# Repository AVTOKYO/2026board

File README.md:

# AVTOKYO 2026 Hackable Board

[English](README_EN.md)

no drink, no hack

| 未実装の基板（裏面・表面） | 赤LEDを付けた作例 |
|---|---|
|  |  |

**Assembly guide / 作り方 — [日本語](docs/ASSEMBLY_JA.md) · [English](docs/ASSEMBLY_EN.md)**

AVTOKYOのドット絵ロゴをモチーフにした、自由に工作・改造して楽しむPCBです。部品を付けずにチャームとして使うのも、LEDや好きな回路を追加するのも自由です。

組み立て説明では、赤いLEDを2個点灯させるシンプルな例を紹介しています。ATtiny402を追加すると、プログラムで点滅を変えられます。

**LEDを付けてみたい方は、[基本の作り方](docs/ASSEMBLY_JA.md)をご覧ください。**

| 内容 | ファイル |
|---|---|
| 基本の組み立て | [組立説明書](docs/ASSEMBLY_JA.md) |
| 用意する部品 | [部品表](docs/PARTS_JA.md) |
| MCUを追加する工作 | [改造ガイド](docs/HACK_JA.md) |
| 書き込みと点滅プログラム | [ファームウェア説明](firmware/README_JA.md) |
| 裏蓋・ケース | [固定方法・STL](case/README.md) |
| 基板を発注する | [製造手順](manufacturing/README.md) |
| 最終製造用データ | [Rev M Gerber ZIP](manufacturing/AVTOKYO_LED_Charm_RevM_FINAL_JLCPCB.zip) |
| 編集する基板データ | [KiCad PCB](hardware/AVTOKYO_LED_Charm.kicad_pcb)・[回路図](hardware/AVTOKYO_LED_Charm.kicad_sch) |

回路図・基板データはKiCad 10で保存しています。ファイル一式をダウンロードしてから、hardware内のプロジェクトを開いてください。

## 確認状況

製造用データは回路図との照合を含むDRC・ERCを通過しています。検査結果はvalidationに収録しています。Rev Mの実機組立・MCU書込については最終確認結果が未記録です。

## ライセンスと改造

製作・改造・再配布・販売は、各ライセンスの条件に従って自由に行えます。[ライセンスの説明](docs/LICENSE_JA.md)と[ロゴ利用条件](LOGO_POLICY.md)をご覧ください。ケースSTLも、作者の同意により基板と同じCERN-OHL-P-2.0です。

組み立て説明は最もシンプルな構成の一例です。LEDの変更や部品の追加、MCUによる点滅など、自由に改造して楽しんでください。

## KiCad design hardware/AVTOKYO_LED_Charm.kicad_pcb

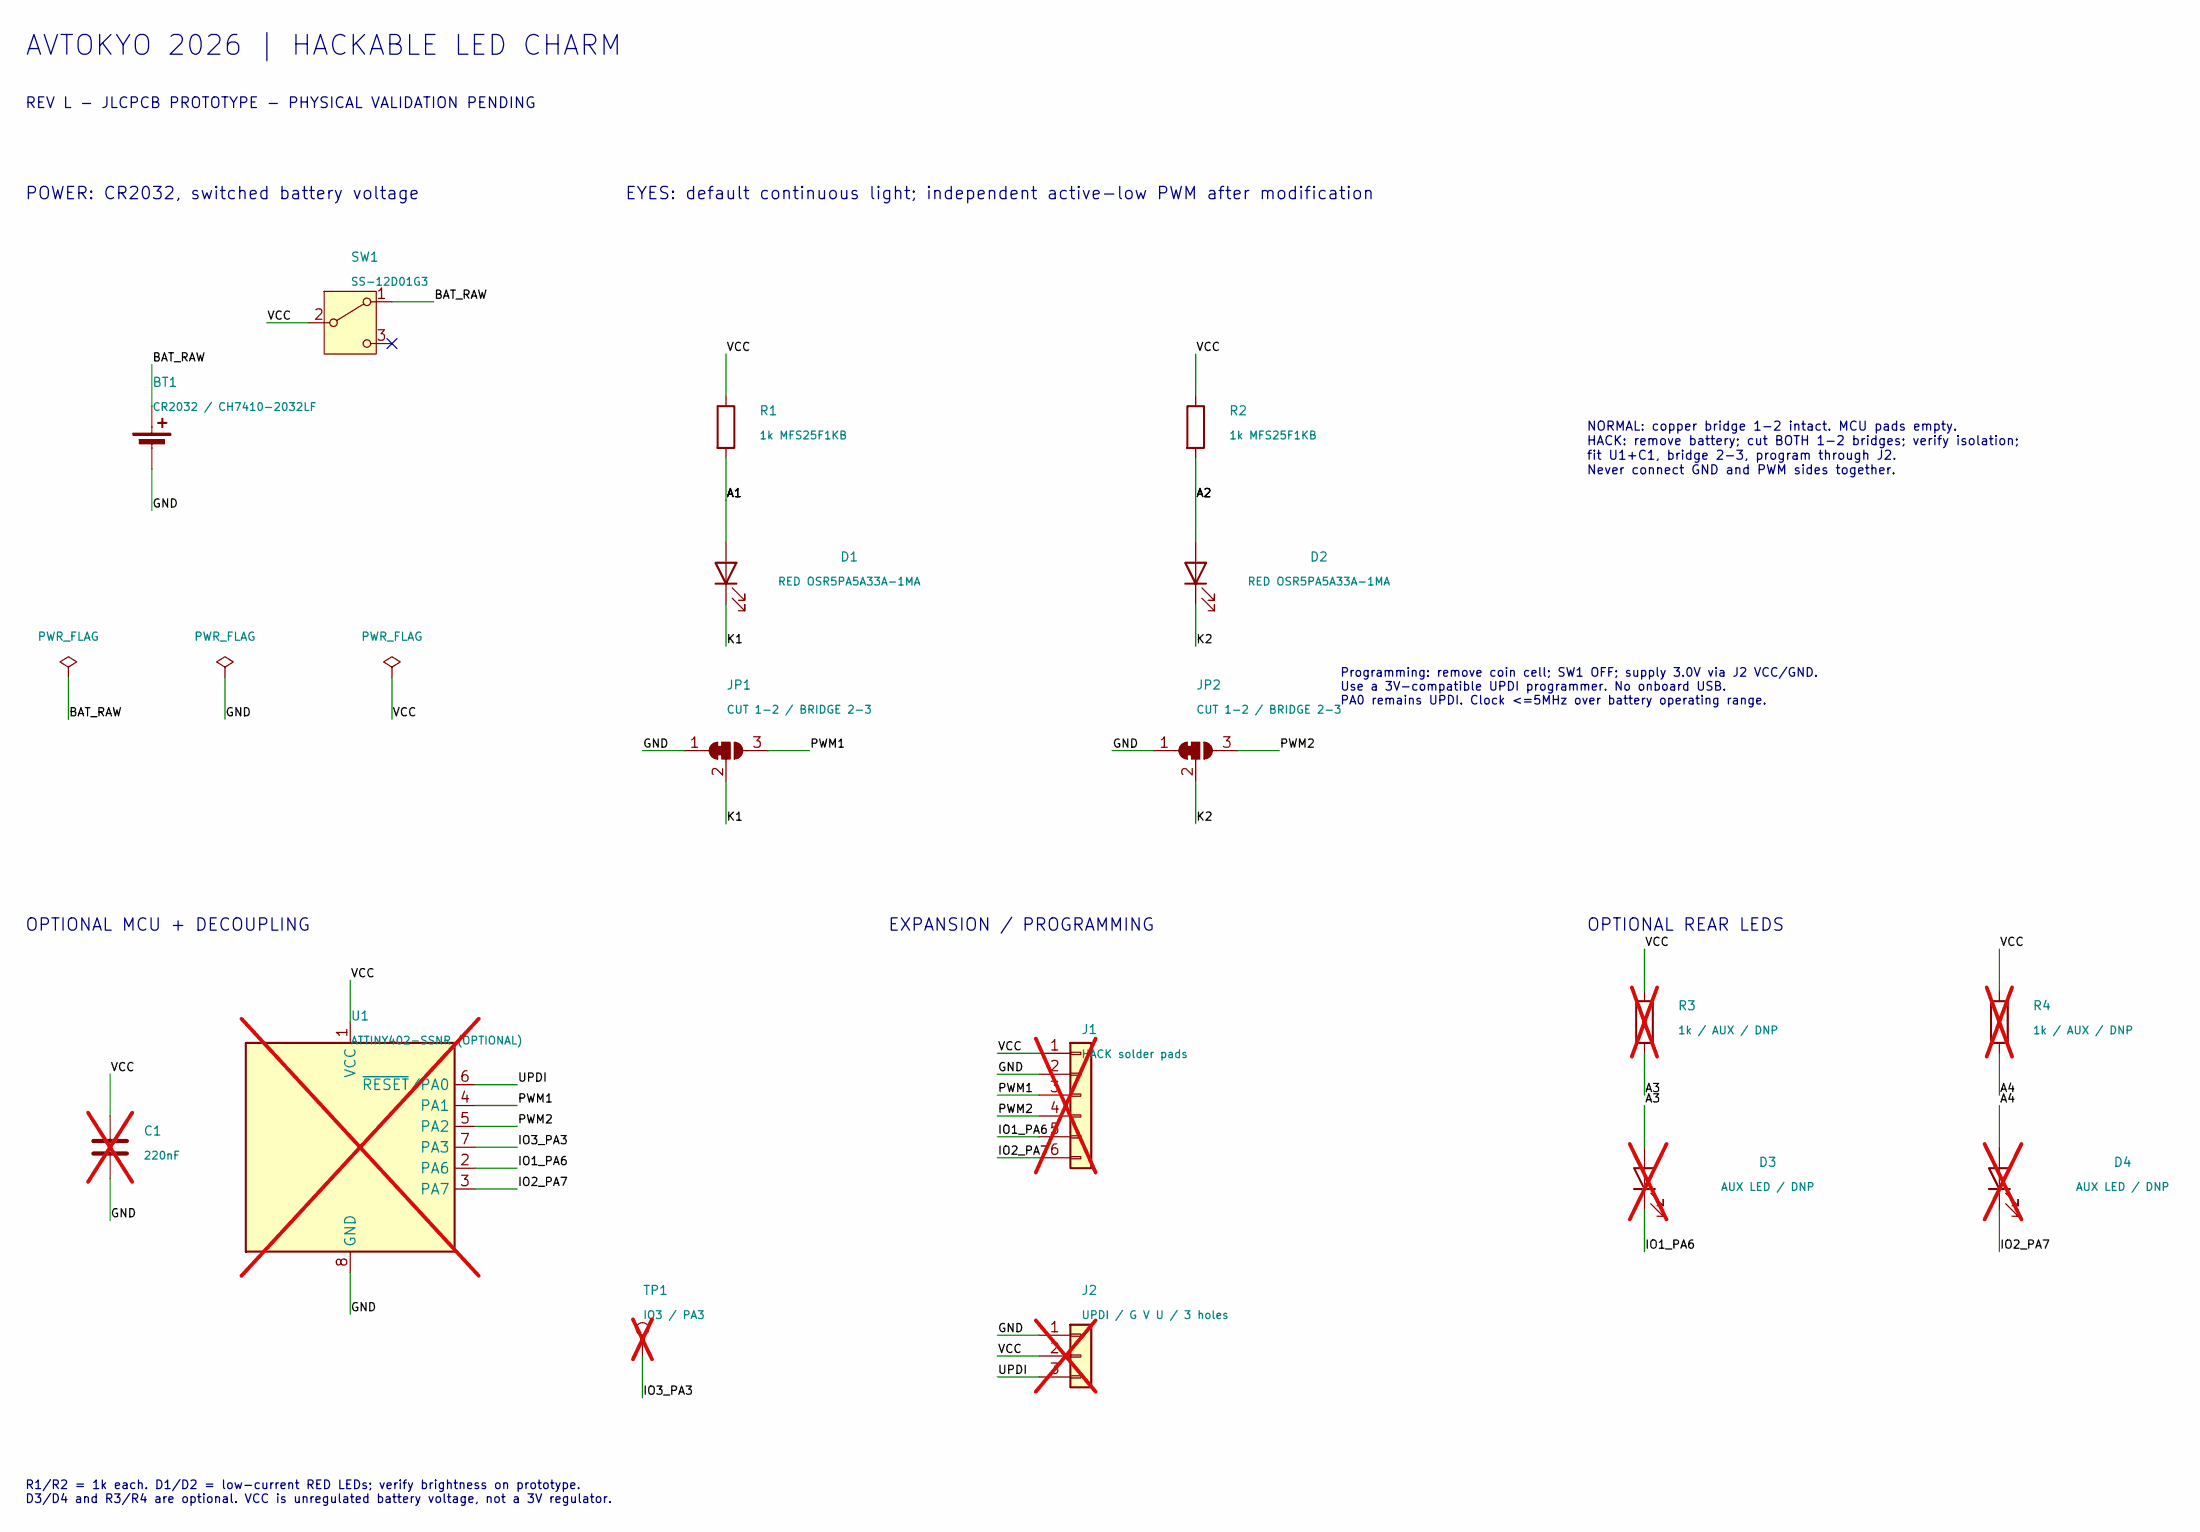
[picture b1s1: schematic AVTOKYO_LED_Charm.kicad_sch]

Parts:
BT1: CR2032 / CH7410-2032LF; BatteryHolder_CH7410_2032LF
C1: 220nF; C_0805_2012Metric_Pad1.18x1.45mm_HandSolder; not fitted
D1, D2: RED OSR5PA5A33A-1MA; LED_D5.0mm
D3, D4: AUX LED / DNP; LED_0805_2012Metric_Pad1.15x1.40mm_HandSolder; not fitted
J1: HACK solder pads; SolderPort_1x06_P2mm; not fitted
J2: UPDI / G V U / 3 holes; UPDI_1x03_P2.54mm_THT; not fitted
JP1, JP2: CUT 1-2 / BRIDGE 2-3; SolderJumper-3_P1.3mm_Bridged12_Pad1.0x1.5mm
R1, R2: 1k MFS25F1KB; R_Axial_DIN0204_L3.6mm_D1.6mm_P7.62mm_Horizontal
R3, R4: 1k / AUX / DNP; R_0805_2012Metric_Pad1.20x1.40mm_HandSolder; not fitted
SW1: SS-12D01G3; SW_SS12D01G3_RightAngle
TP1: IO3 / PA3; TestPoint_Pad_D1.5mm; not fitted
U1: ATTINY402-SSNR (OPTIONAL); SOIC-8_3.9x4.9mm_P1.27mm; not fitted

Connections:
/A1: D1.2 (A), R1.2
/A2: D2.2 (A), R2.2
/A3: D3.2 (A), R3.2
/A4: D4.2 (A), R4.2
/BAT_RAW: BT1.1 (+), SW1.1 (A)
/GND: BT1.2 (-), C1.2, J1.2, J2.1, JP1.1 (A), JP2.1 (A), U1.8 (GND)
/IO1_PA6: D3.1 (K), J1.5, U1.2 (PA6)
/IO2_PA7: D4.1 (K), J1.6, U1.3 (PA7)
/IO3_PA3: TP1.1, U1.7 (PA3)
/K1: D1.1 (K), JP1.2 (C)
/K2: D2.1 (K), JP2.2 (C)
/PWM1: J1.3, JP1.3 (B), U1.4 (PA1)
/PWM2: J1.4, JP2.3 (B), U1.5 (PA2)
/UPDI: J2.3, U1.6 (~RESET/PA0)
/VCC: C1.1, J1.1, J2.2, R1.1, R2.1, R3.1, R4.1, SW1.2 (B), U1.1 (VCC)

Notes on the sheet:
AVTOKYO 2026 | HACKABLE LED CHARM
REV L - JLCPCB PROTOTYPE - PHYSICAL VALIDATION PENDING
POWER: CR2032, switched battery voltage
EYES: default continuous light; independent active-low PWM after modification
OPTIONAL MCU + DECOUPLING
EXPANSION / PROGRAMMING
OPTIONAL REAR LEDS
NORMAL: copper bridge 1-2 intact. MCU pads empty. HACK: remove battery; cut BOTH 1-2 bridges; verify isolation; fit U1+C1, bridge 2-3, program through J2. Never connect GND and PWM sides together.
Programming: remove coin cell; SW1 OFF; supply 3.0V via J2 VCC/GND. Use a 3V-compatible UPDI programmer. No onboard USB. PA0 remains UPDI. Clock <=5MHz over battery operating range.
R1/R2 = 1k each. D1/D2 = low-current RED LEDs; verify brightness on prototype. D3/D4 and R3/R4 are optional. VCC is unregulated battery voltage, not a 3V regulator.

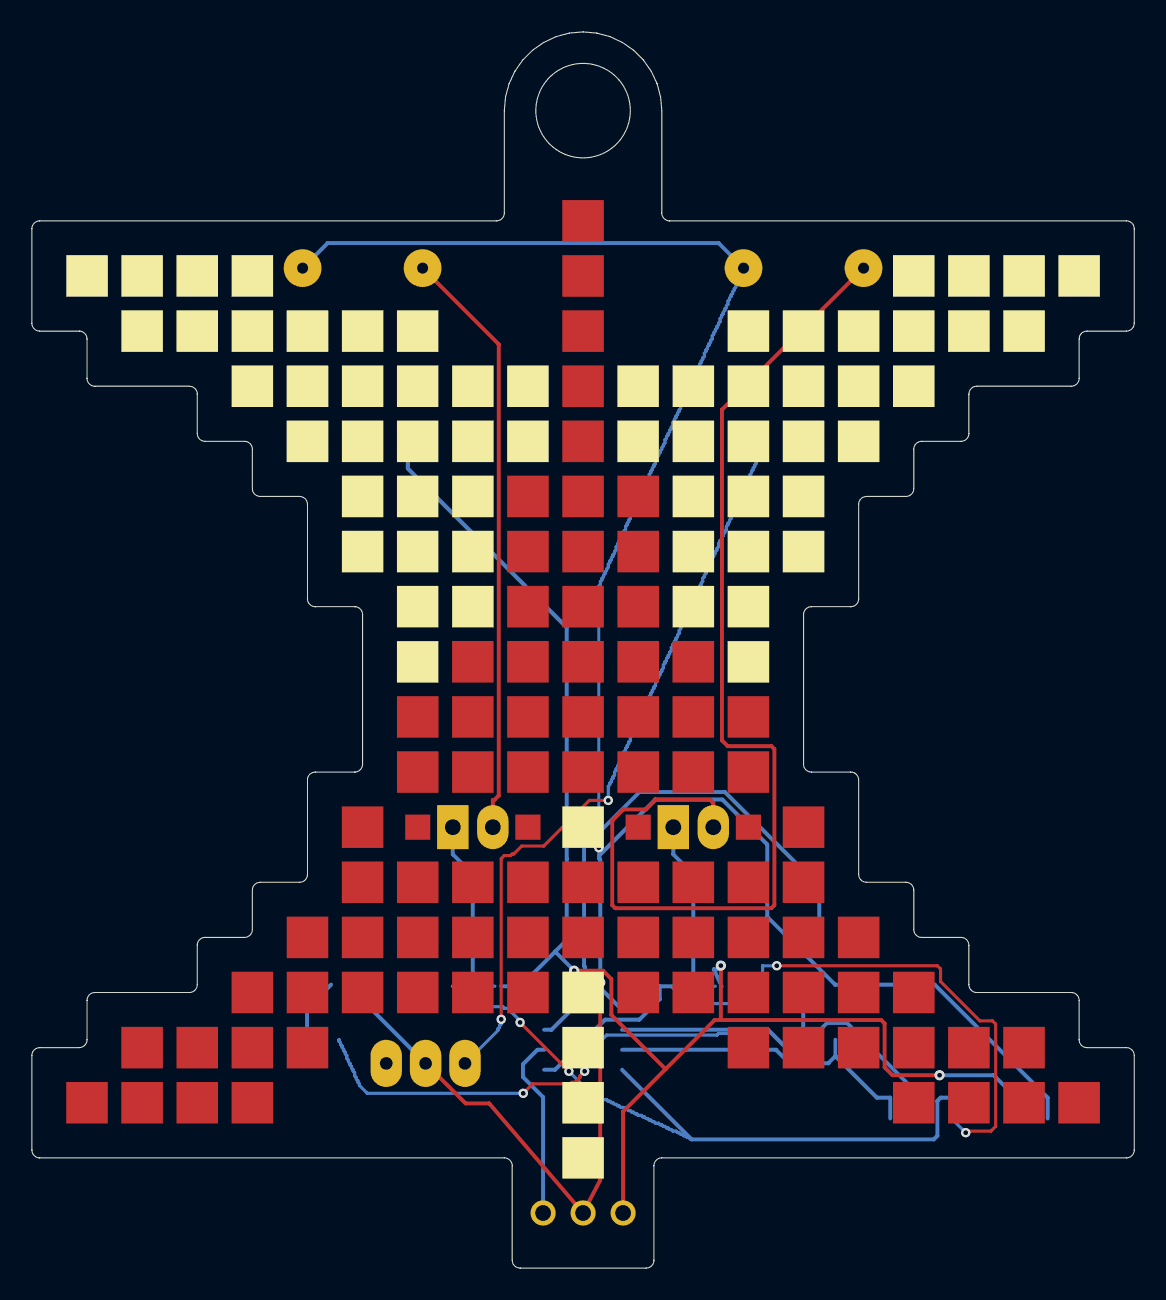
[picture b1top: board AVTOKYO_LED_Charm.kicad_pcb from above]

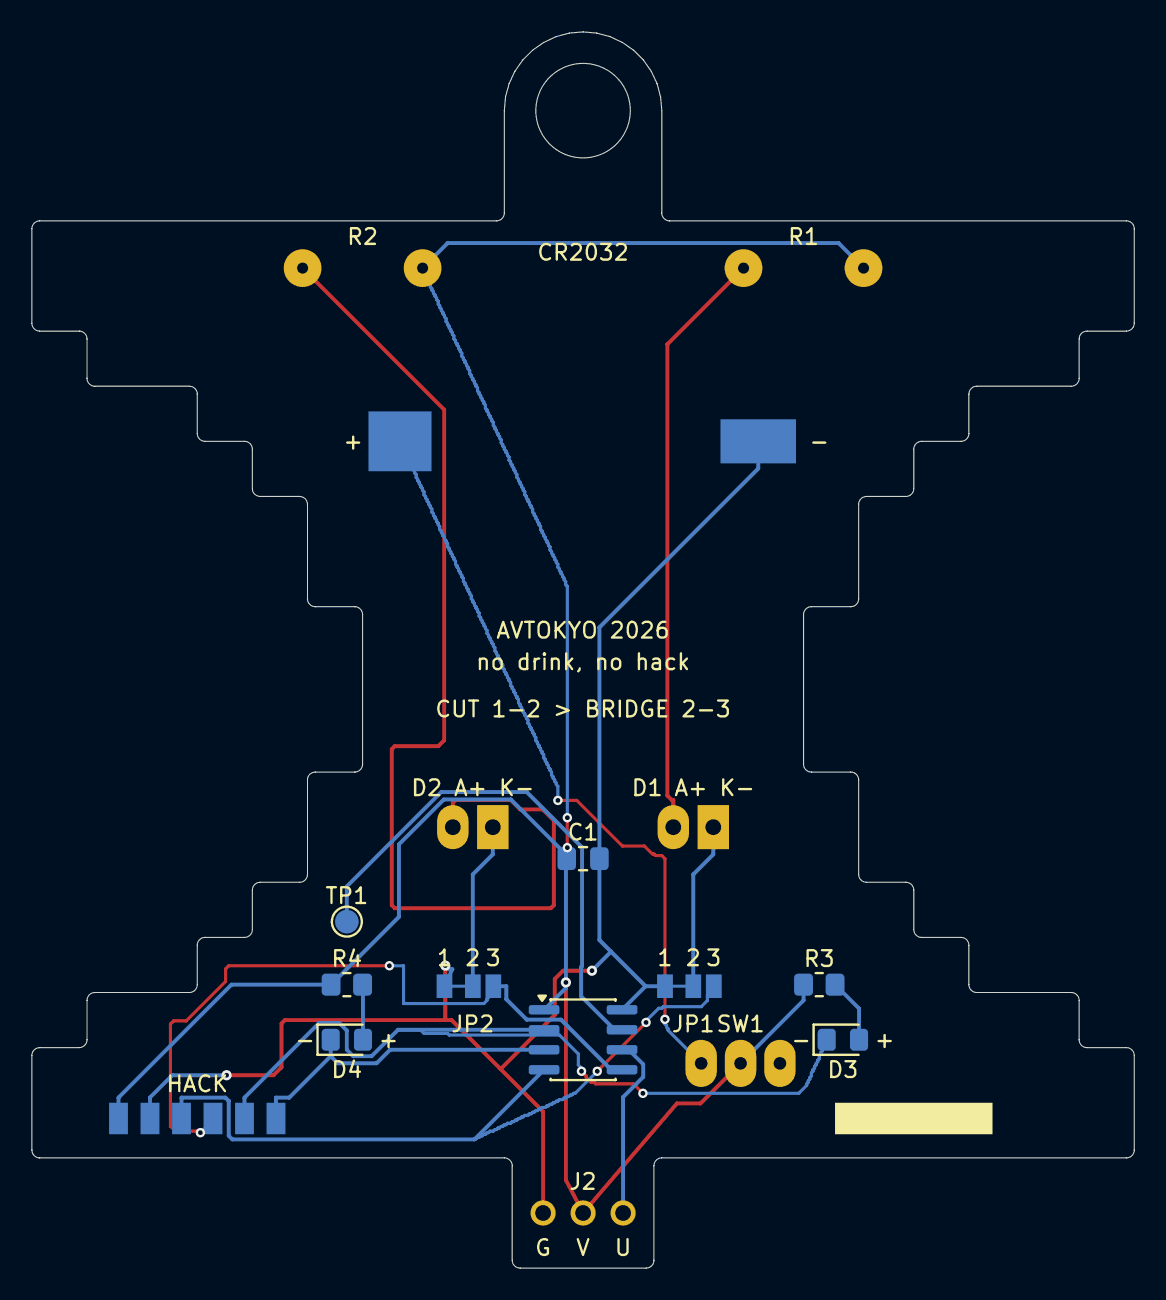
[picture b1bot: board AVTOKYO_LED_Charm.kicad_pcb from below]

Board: 2 copper layers, 70.0 x 78.5 mm, 19 parts (13 on the bottom side), 15 nets.

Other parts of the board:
H1: Hook_6mm
LOGO: Original_Pixels

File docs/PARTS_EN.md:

# Parts list — Rev M

[日本語](PARTS_JA.md) · [Project overview](../README_EN.md)

## Basic assembly: one board

| Reference | Part | Quantity | Reference link |
|---|---|---:|---|
| R1, R2 | Small metal film resistor, 1kΩ, 1/4W, MFS25F1KB | 2 | [Akizuki 108535](https://akizukidenshi.com/catalog/g/g108535/) |
| D1, D2 | 5mm low-current red LED, OSR5PA5A33A-1MA | 2 | [Akizuki 116914](https://akizukidenshi.com/catalog/g/g116914/) |
| BT1 | CR2032 holder, CH7410-2032LF | 1 | [Akizuki 102684](https://akizukidenshi.com/catalog/g/g102684/) |
| SW1 | Slide switch, SS-12D01G3 | 1 | [Akizuki 115704](https://akizukidenshi.com/catalog/g/g115704/) |
| Battery | CR2032, 3V, non-rechargeable | 1 | Commonly available |

The resistor holes are 7.62mm apart center to center. Use small resistors whose bodies fit this spacing. If substituting a CH28 holder or SS12D01G4 switch, check terminal locations and board compatibility separately.

## MCU and optional modifications

| Reference | Part | Quantity |
|---|---|---:|
| U1 | ATTINY402-SSNR, SOIC-8 | 1 |
| C1 | 0.22µF, 16V ceramic capacitor, metric 2012 (0805) | 1 |
| J2 | Optional 3-pin header, 2.54mm pitch | 1 |
| D3, D4 | Low-forward-voltage LEDs, metric 2012 (0805) | Up to 2 |
| R3, R4 | Resistors, metric 2012 (0805); start with 1kΩ for low-current red LEDs and verify operation | Up to 2 |
| Shared equipment | ATtiny402-compatible UPDI programmer with 3.3V target power and signals | 1 |

Pair D3 with R3 and D4 with R4, and control the corresponding GPIO pins in your firmware.

Supplier links identify the parts. Check stock and pricing with the supplier.

## Optional rear cover

![Rear cover](images/case.jpg)

| Item | Part |
|---|---|
| Rear cover | [STL file](../case/case.stl) |
| Fastening screw | M1 × 3mm; secures the lower part of the cover |

See the [case instructions](../case/README_EN.md). Screw quantity, head style, and thread type are not yet specified.

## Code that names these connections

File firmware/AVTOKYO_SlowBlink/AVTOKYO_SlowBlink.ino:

// AVTOKYO Rev K/L, ATtiny402, megaTinyCore, internal 5 MHz, UPDI enabled.
// LED cathodes: D1 -> PA1 (physical pin 4), D2 -> PA2 (pin 5).
// Both jumpers: CUT 1-2, bridge 2-3. LOW lights the LEDs.
#include <Arduino.h>
#if !defined(__AVR_ATtiny402__)
#error "Select ATtiny402 in megaTinyCore"
#endif
constexpr uint8_t LED1 = PIN_PA1;
constexpr uint8_t LED2 = PIN_PA2;
constexpr unsigned long ON_MS = 1000;
constexpr unsigned long OFF_MS = 2000;
void setup() {
  digitalWrite(LED1, HIGH);
  digitalWrite(LED2, HIGH);
  pinMode(LED1, OUTPUT);
  pinMode(LED2, OUTPUT);
  // PA0 remains UPDI. All other optional GPIO remain inputs.
}
void loop() {
  digitalWrite(LED1, LOW);
  digitalWrite(LED2, LOW);
  delay(ON_MS);
  digitalWrite(LED1, HIGH);
  digitalWrite(LED2, HIGH);
  delay(OFF_MS);
}
